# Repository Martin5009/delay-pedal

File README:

A 16-bit, FPGA-based digital delay pedal implementation.

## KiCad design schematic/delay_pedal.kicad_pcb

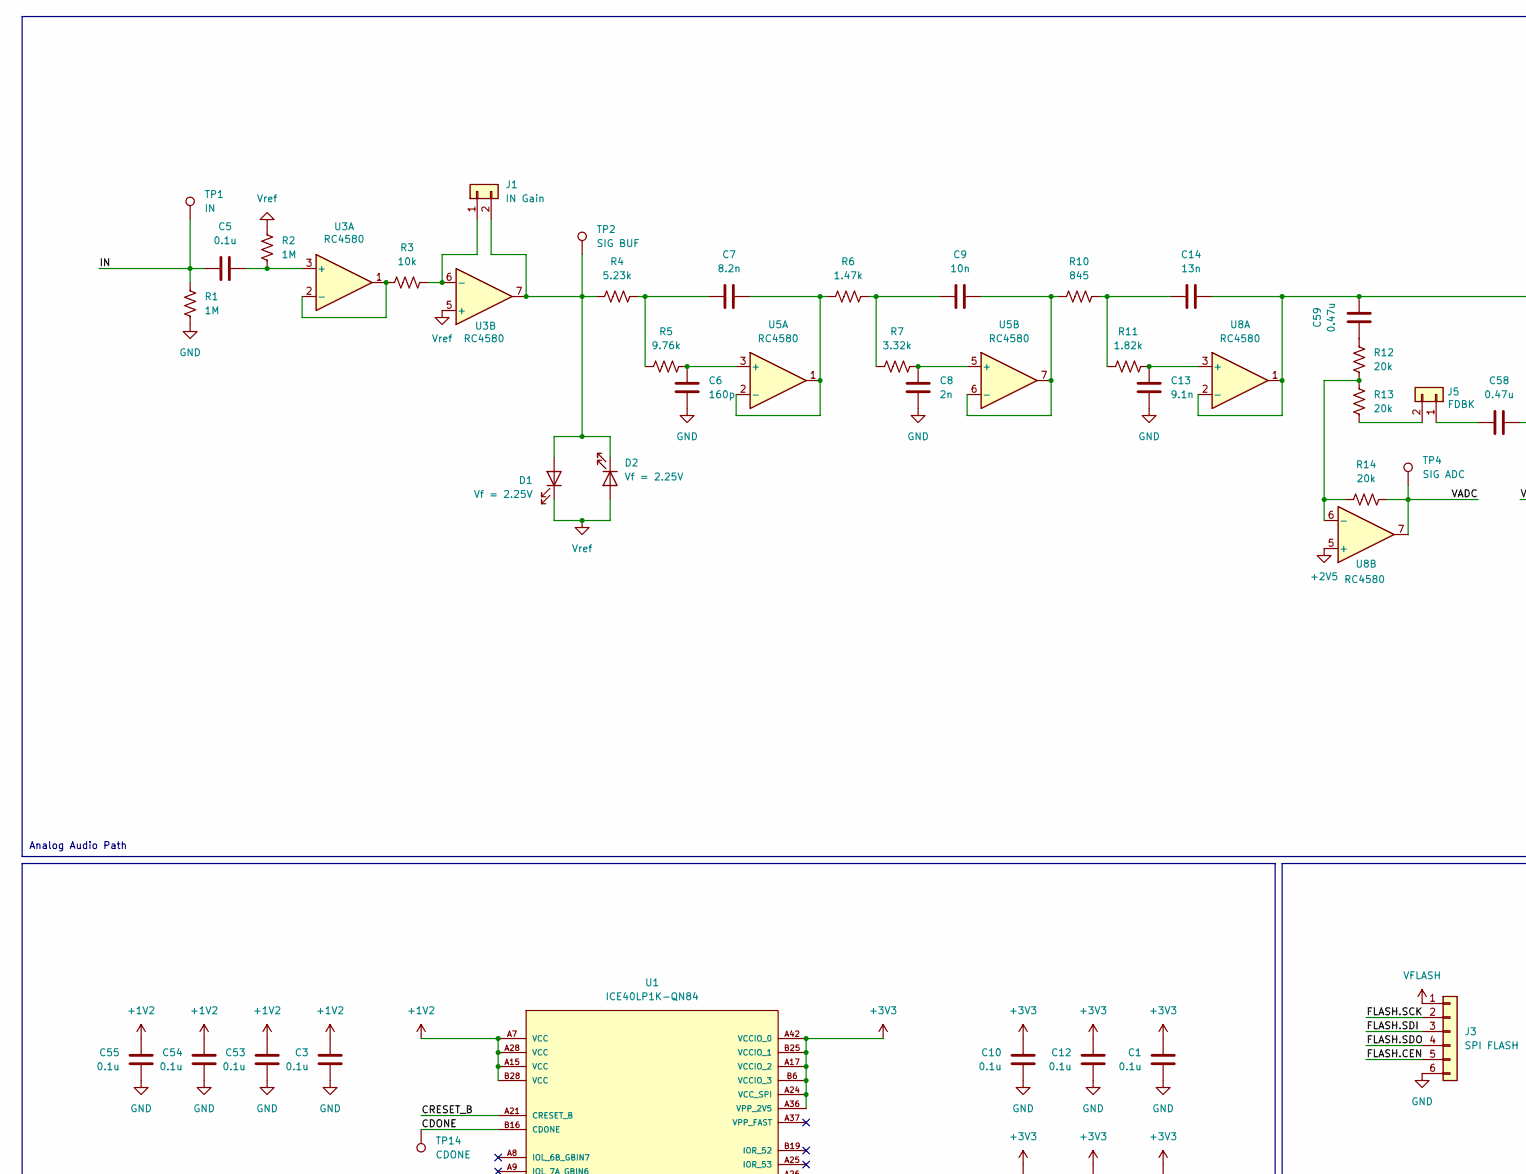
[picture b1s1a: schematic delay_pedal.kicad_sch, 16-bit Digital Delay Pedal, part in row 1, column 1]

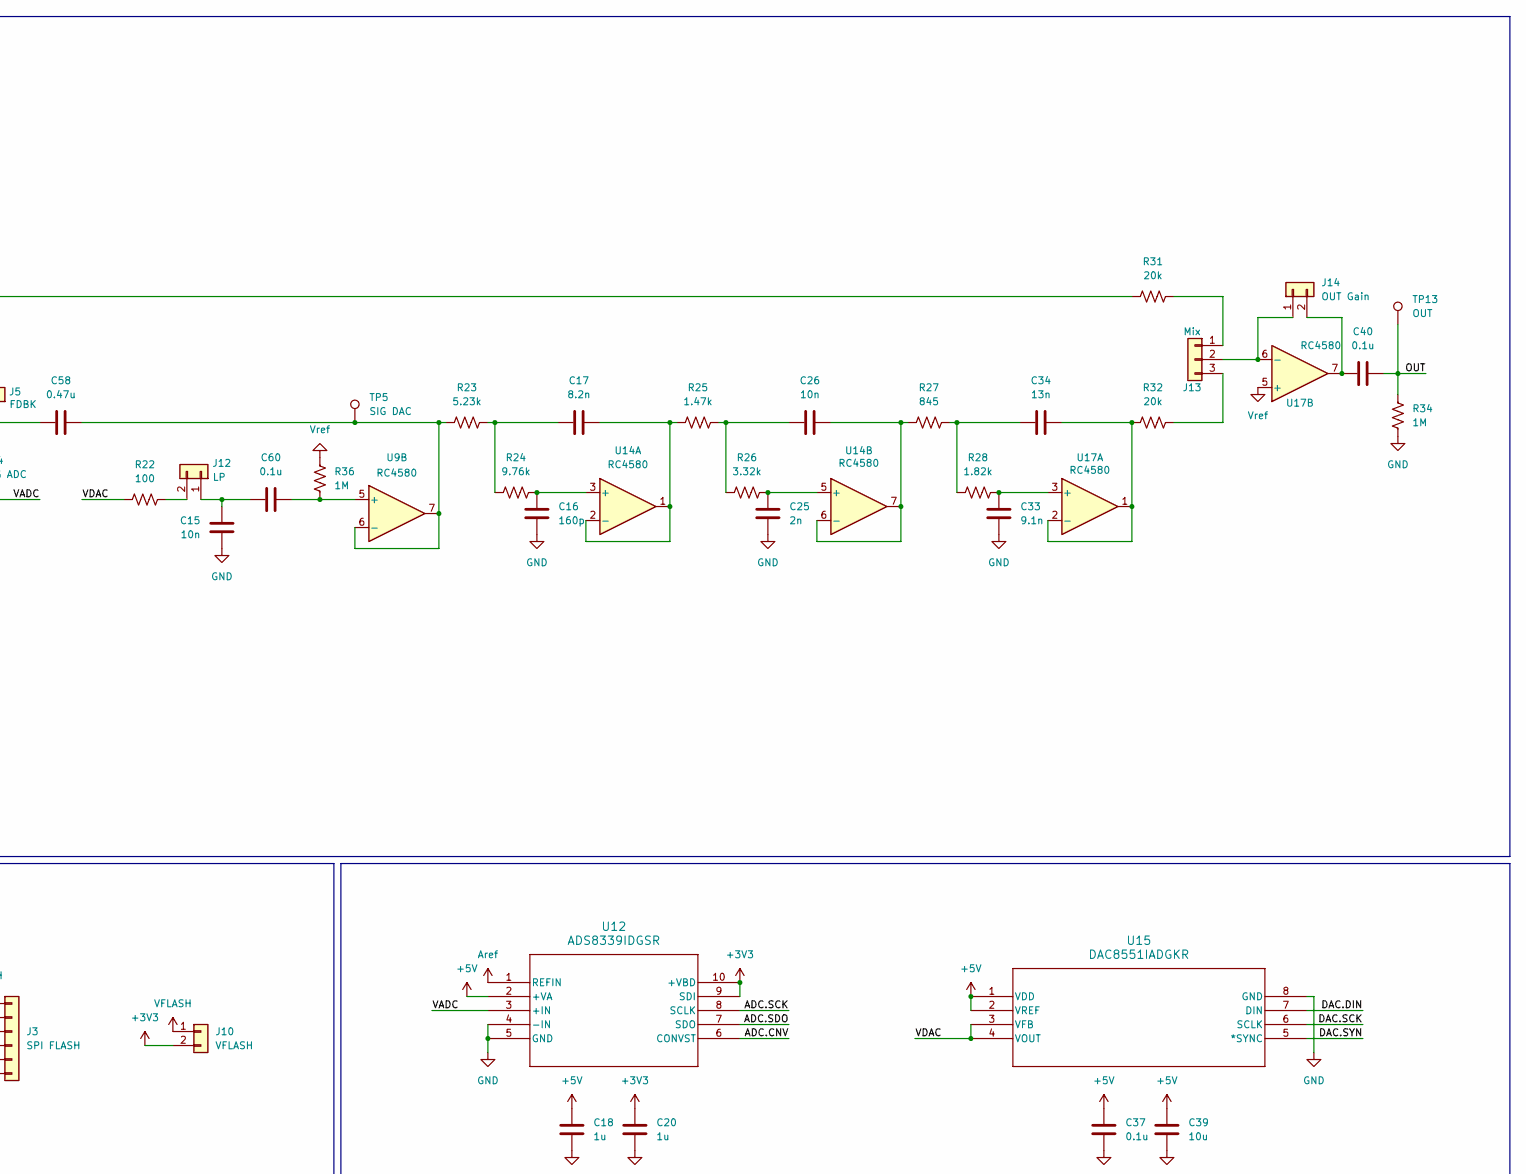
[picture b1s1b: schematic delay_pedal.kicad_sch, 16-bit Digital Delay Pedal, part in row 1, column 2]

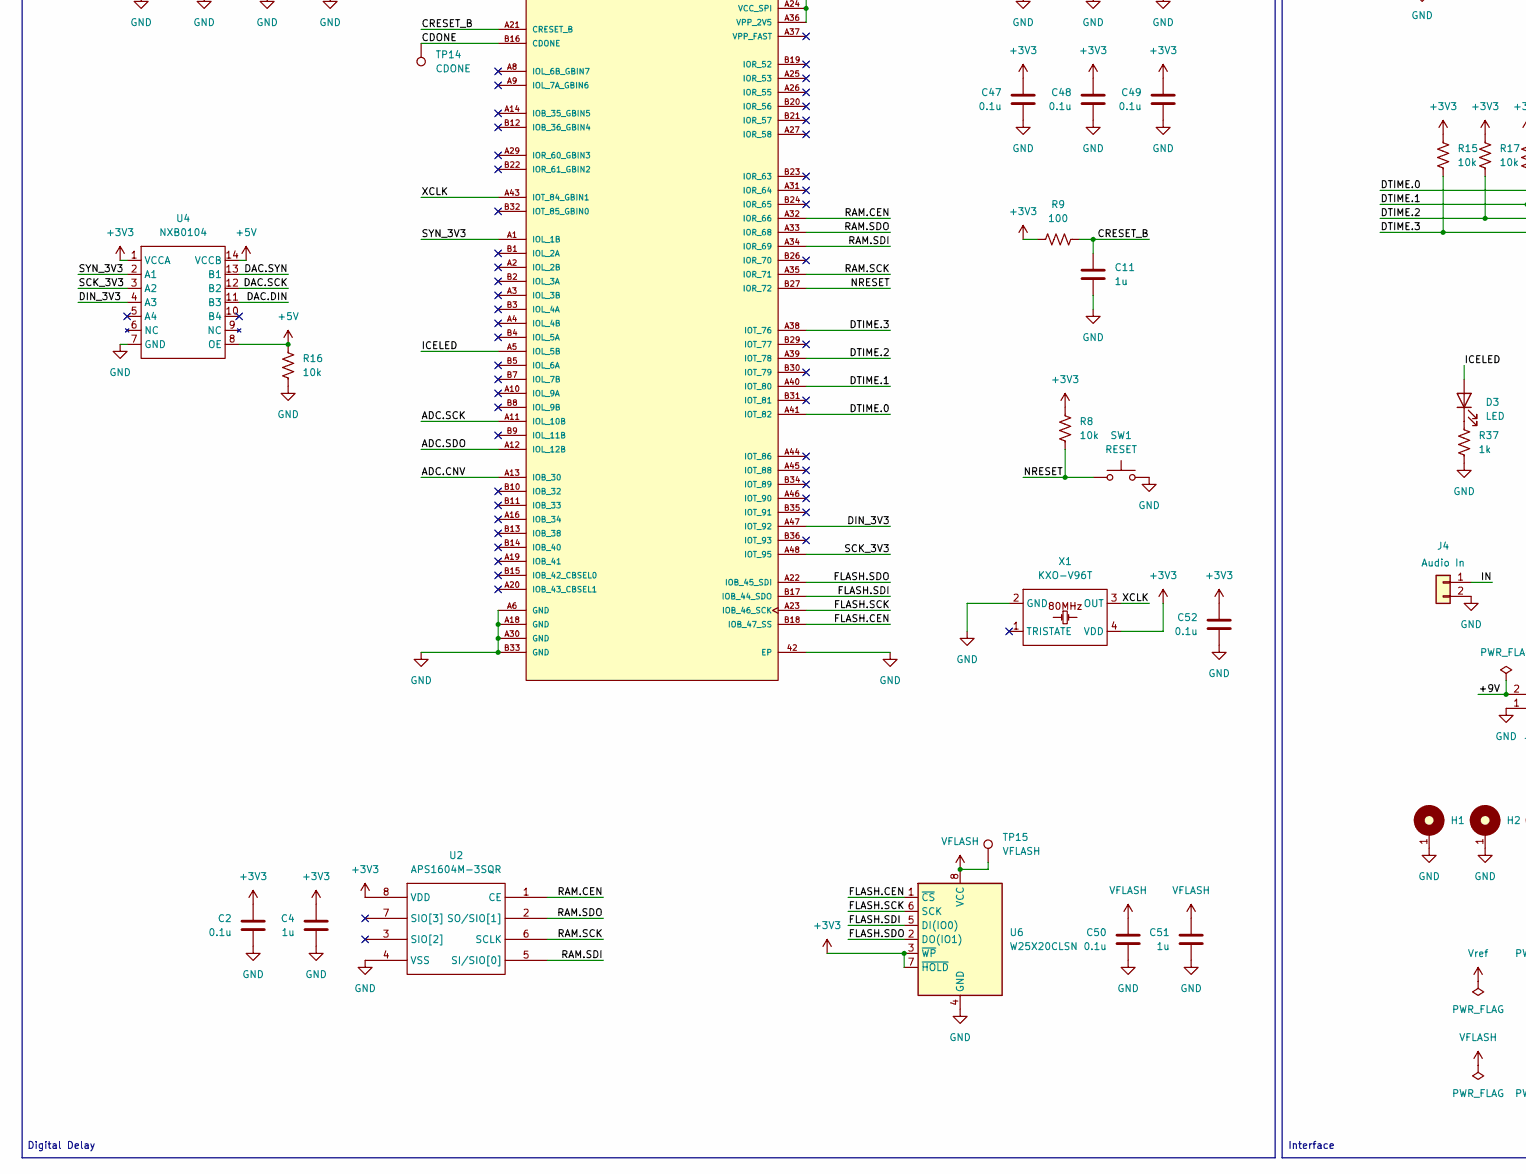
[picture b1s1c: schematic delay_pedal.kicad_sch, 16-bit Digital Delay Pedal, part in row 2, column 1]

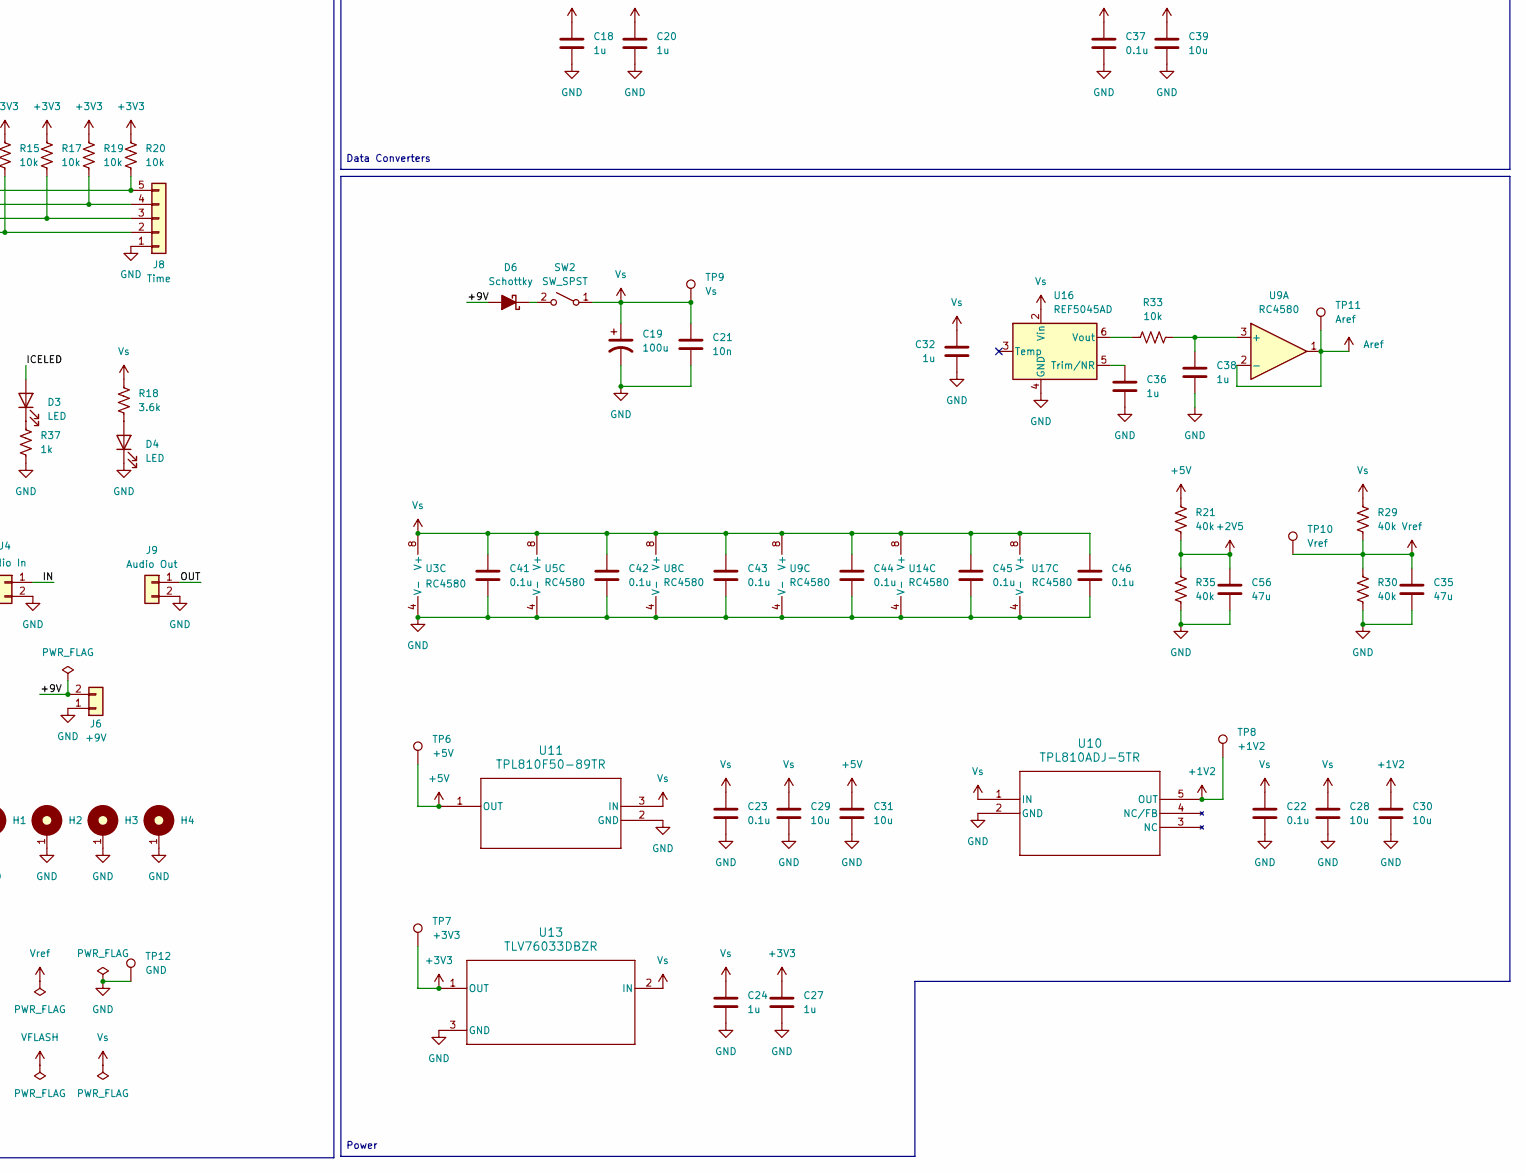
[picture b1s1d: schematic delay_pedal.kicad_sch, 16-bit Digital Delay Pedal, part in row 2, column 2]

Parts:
C1, C2, C3, C10, C12, C22, C23, C37, C41, C42, C43, C44, C45, C46, C47, C48, C49, C50, C52, C53, C54, C55: 0.1u; C_0603_1608Metric_Pad1.08x0.95mm_HandSolder
C4, C11, C18, C20, C24, C27, C32, C36, C38, C51: 1u; C_0603_1608Metric_Pad1.08x0.95mm_HandSolder
C5, C40, C60: 0.1u; C_1206_3216Metric_Pad1.33x1.80mm_HandSolder
C6, C16: 160p; C_0603_1608Metric_Pad1.08x0.95mm_HandSolder
C7, C17: 8.2n; C_0603_1608Metric_Pad1.08x0.95mm_HandSolder
C8, C25: 2n; C_0603_1608Metric_Pad1.08x0.95mm_HandSolder
C9, C15, C21, C26: 10n; C_0603_1608Metric_Pad1.08x0.95mm_HandSolder
C13, C33: 9.1n; C_0603_1608Metric_Pad1.08x0.95mm_HandSolder
C14, C34: 13n; C_0603_1608Metric_Pad1.08x0.95mm_HandSolder
C19: 100u; CP_Radial_D6.3mm_P2.50mm
C28, C29, C30, C31, C39: 10u; C_0603_1608Metric_Pad1.08x0.95mm_HandSolder
C35, C56: 47u; C_0603_1608Metric_Pad1.08x0.95mm_HandSolder
C58, C59: 0.47u; C_0603_1608Metric_Pad1.08x0.95mm_HandSolder
D1, D2: Vf = 2.25V; LED_0603_1608Metric_Pad1.05x0.95mm_HandSolder
D3, D4: LED; LED_0603_1608Metric_Pad1.05x0.95mm_HandSolder
D6: Schottky; D_SOD-323_HandSoldering
H1, H2, H3, H4: MountingHole_M3_3.2mm_Pad; MountingHole_3.2mm_Pad
J1: IN Gain; PinHeader_1x02_P2.54mm_Vertical
J3: SPI FLASH; PinHeader_1x06_P2.54mm_Vertical
J4: Audio In; PinHeader_1x02_P2.54mm_Vertical
J5: FDBK; PinHeader_1x02_P2.54mm_Vertical
J6: +9V; PinHeader_1x02_P2.54mm_Vertical
J8: Time; PinHeader_1x05_P2.54mm_Vertical
J9: Audio Out; PinHeader_1x02_P2.54mm_Vertical
J10: VFLASH; PinHeader_1x02_P2.54mm_Vertical
J12: LP; PinHeader_1x02_P2.54mm_Vertical
J13: Mix; PinHeader_1x03_P2.54mm_Vertical
J14: OUT Gain; PinHeader_1x02_P2.54mm_Vertical
R1, R2, R34, R36: 1M; R_0603_1608Metric_Pad0.98x0.95mm_HandSolder
R3, R8, R15, R16, R17, R19, R20, R33: 10k; R_0603_1608Metric_Pad0.98x0.95mm_HandSolder
R4, R23: 5.23k; R_0603_1608Metric_Pad0.98x0.95mm_HandSolder
R5, R24: 9.76k; R_0603_1608Metric_Pad0.98x0.95mm_HandSolder
R6, R25: 1.47k; R_0603_1608Metric_Pad0.98x0.95mm_HandSolder
R7, R26: 3.32k; R_0603_1608Metric_Pad0.98x0.95mm_HandSolder
R9, R22: 100; R_0603_1608Metric_Pad0.98x0.95mm_HandSolder
R10, R27: 845; R_0603_1608Metric_Pad0.98x0.95mm_HandSolder
R11, R28: 1.82k; R_0603_1608Metric_Pad0.98x0.95mm_HandSolder
R12, R13, R14, R31, R32: 20k; R_0603_1608Metric_Pad0.98x0.95mm_HandSolder
R18: 3.6k; R_0603_1608Metric_Pad0.98x0.95mm_HandSolder
R21, R29, R30, R35: 40k; R_0603_1608Metric_Pad0.98x0.95mm_HandSolder
R37: 1k; R_0603_1608Metric_Pad0.98x0.95mm_HandSolder
SW1: RESET; SW_PUSH_1P1T_6x3.5mm_H4.3_APEM_MJTP1243
SW2: SW_SPST; PinHeader_1x02_P2.54mm_Vertical
TP1: IN; TestPoint_THTPad_D1.0mm_Drill0.5mm
TP2: SIG BUF; TestPoint_THTPad_D1.0mm_Drill0.5mm
TP4: SIG ADC; TestPoint_THTPad_D1.0mm_Drill0.5mm
TP5: SIG DAC; TestPoint_THTPad_D1.0mm_Drill0.5mm
TP6: +5V; TestPoint_THTPad_D1.0mm_Drill0.5mm
TP7: +3V3; TestPoint_THTPad_D1.0mm_Drill0.5mm
TP8: +1V2; TestPoint_THTPad_D1.0mm_Drill0.5mm
TP9: Vs; TestPoint_THTPad_D1.0mm_Drill0.5mm
TP10: Vref; TestPoint_THTPad_D1.0mm_Drill0.5mm
TP11: Aref; TestPoint_THTPad_D1.0mm_Drill0.5mm
TP12: GND; TestPoint_THTPad_D1.0mm_Drill0.5mm
TP13: OUT; TestPoint_THTPad_D1.0mm_Drill0.5mm
TP14: CDONE; TestPoint_THTPad_D1.0mm_Drill0.5mm
TP15: VFLASH; TestPoint_THTPad_D1.0mm_Drill0.5mm
U1: ICE40LP1K-QN84; LATTICE_ICE40LP1K-QN84; PARTREV 3.4; DigiKey_Part_Number 220-1561-ND
U2: APS1604M-3SQR; SOP-8_3.9x4.9mm_P1.27mm
U3, U5, U8, U9, U14, U17: RC4580; SOIC-8_3.9x4.9mm_P1.27mm
U4: NXB0104; TSSOP-14_4.4x5mm_P0.65mm
U6: W25X20CLSN; SOIC-8_3.9x4.9mm_P1.27mm
U10: TPL810ADJ-5TR; SOT-23-5_HandSoldering
U11: TPL810F50-89TR; SOT-89-3_Handsoldering
U12: ADS8339IDGSR; VSSOP-10_3x3mm_P0.5mm
U13: TLV76033DBZR; SOT-89-3_Handsoldering
U15: DAC8551IADGKR; VSSOP-8_3x3mm_P0.65mm
U16: REF5045AD; SOIC-8_3.9x4.9mm_P1.27mm
X1: KXO-V96T; Oscillator_SMD_Abracon_ASE-4Pin_3.2x2.5mm

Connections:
+1V2: C3.1, C30.1, C53.1, C54.1, C55.1, TP8.1, U1.A7 (VCC), U1.A15 (VCC), U1.A28 (VCC), U1.B28 (VCC), U10.5 (OUT)
+2V5: C56.1, R21.2, R35.1, U8.5 (+)
+3V3: C1.1, C2.1, C4.1, C10.1, C12.1, C20.1, C27.1, C47.1, C48.1, C49.1, C52.1, J10.2, R8.1, R9.2, R15.1, R17.1, R19.1, R20.1, TP7.1, U1.A17 (VCCIO_2), U1.A24 (VCC_SPI), U1.A36 (VPP_2V5), U1.A42 (VCCIO_0), U1.B6 (VCCIO_3), U1.B25 (VCCIO_1), U2.8 (VDD), U4.1 (VCCA), U6.3 (~WP), U6.7 (~HOLD), U12.9 (SDI), U12.10 (+VBD), U13.1 (OUT), X1.4 (VDD)
+5V: C18.1, C31.1, C37.1, C39.1, R16.1, R21.1, TP6.1, U4.8 (OE), U4.14 (VCCB), U11.1 (OUT), U12.2 (+VA), U15.1 (VDD), U15.2 (VREF)
/+9V: D6.2 (A), J6.2
/ADC.CNV: U1.A13 (IOB_30), U12.6 (CONVST)
/ADC.SCK: U1.A11 (IOL_10B), U12.8 (SCLK)
/ADC.SDO: U1.A12 (IOL_12B), U12.7 (SDO)
/CDONE: TP14.1, U1.B16 (CDONE)
/CRESET_B: C11.1, R9.1, U1.A21 (CRESET_B)
/DAC.DIN: U4.11 (B3), U15.7 (DIN)
/DAC.SCK: U4.12 (B2), U15.6 (SCLK)
/DAC.SYN: U4.13 (B1), U15.5 (*SYNC)
/DIN_3V3: U1.A47 (IOT_92), U4.4 (A3)
/DTIME.0: J8.5, R20.2, U1.A41 (IOT_82)
/DTIME.1: J8.4, R19.2, U1.A40 (IOT_80)
/DTIME.2: J8.3, R17.2, U1.A39 (IOT_78)
/DTIME.3: J8.2, R15.2, U1.A38 (IOT_76)
/FLASH.CEN: J3.5, U1.B18 (IOB_47_SS), U6.1 (~CS)
/FLASH.SCK: J3.2, U1.A23 (IOB_46_SCK), U6.6 (SCK)
/FLASH.SDI: J3.3, U1.B17 (IOB_44_SDO), U6.5 (DI(IO0))
/FLASH.SDO: J3.4, U1.A22 (IOB_45_SDI), U6.2 (DO(IO1))
/ICELED: D3.2 (A), U1.A5 (IOL_5B)
/IN: C5.1, J4.1, R1.1, TP1.1
/NRESET: R8.2, SW1.1, U1.B27 (IOR_72)
/OUT: C40.2, J9.1, R34.1, TP13.1
/RAM.CEN: U1.A32 (IOR_66), U2.1 (CE)
/RAM.SCK: U1.A35 (IOR_71), U2.6 (SCLK)
/RAM.SDI: U1.A34 (IOR_69), U2.5 (SI/SIO[0])
/RAM.SDO: U1.A33 (IOR_68), U2.2 (SO/SIO[1])
/SCK_3V3: U1.A48 (IOT_95), U4.3 (A2)
/SYN_3V3: U1.A1 (IOL_1B), U4.2 (A1)
/VADC: R14.1, TP4.1, U8.7, U12.3 (+IN)
/VDAC: R22.2, U15.3 (VFB), U15.4 (VOUT)
/XCLK: U1.A43 (IOT_84_GBIN1), X1.3 (OUT)
Aref: TP11.1, U9.1, U9.2 (-), U12.1 (REFIN)
GND: C1.2, C2.2, C3.2, C4.2, C6.2, C8.2, C10.2, C11.2, C12.2, C13.2, C15.2, C16.2, C18.2, C19.2, C20.2, C21.2, C22.2, C23.2, C24.2, C25.2, C27.2, C28.2, C29.2, C30.2, C31.2, C32.2, C33.2, C35.2, C36.2, C37.2, C38.2, C39.2, C41.2, C42.2, C43.2, C44.2, C45.2, C46.2, C47.2, C48.2, C49.2, C50.2, C51.2, C52.2, C53.2, C54.2, C55.2, C56.2, D4.1 (K), H1.1, H2.1, H3.1, H4.1, J3.6, J4.2, J6.1, J8.1, J9.2, R1.2, R16.2, R30.2, R34.2, R35.2, R37.2, SW1.2, TP12.1, U1.42 (EP), U1.A6 (GND), U1.A18 (GND), U1.A30 (GND), U1.B33 (GND), U2.4 (VSS), U3.4 (V-), U4.7 (GND), U5.4 (V-), U6.4 (GND), U8.4 (V-), U9.4 (V-), U10.2 (GND), U11.2 (GND), U12.4 (-IN), U12.5 (GND), U13.3 (GND), U14.4 (V-), U15.8 (GND), U16.4 (GND), U17.4 (V-), X1.2 (GND)
unnamed: C7.1, R4.1, R5.2
unnamed: C9.1, R6.1, R7.2
unnamed: C14.1, R10.1, R11.2
unnamed: C17.1, R23.1, R24.2
unnamed: C26.1, R25.1, R26.2
unnamed: C34.1, R27.1, R28.2
unnamed: C59.1, R12.1
unnamed: D1.2 (A), D2.1 (K), J1.2, R4.2, TP2.1, U3.7
unnamed: D3.1 (K), R37.1
unnamed: D4.2 (A), R18.2
unnamed: D6.1 (K), SW2.2 (B)
unnamed: J1.1, R3.1, U3.6 (-)
unnamed: C58.1, J5.1
unnamed: J5.2, R13.2
unnamed: C15.1, C60.1, J12.1
unnamed: J12.2, R22.1
unnamed: J13.1, R31.1
unnamed: J13.2, J14.1, U17.6 (-)
unnamed: J13.3, R32.1
unnamed: C40.1, J14.2, U17.7
unnamed: C5.2, R2.2, U3.3 (+)
unnamed: R3.2, U3.1, U3.2 (-)
unnamed: C6.1, R5.1, U5.3 (+)
unnamed: C7.2, R6.2, U5.1, U5.2 (-)
unnamed: C8.1, R7.1, U5.5 (+)
unnamed: C9.2, R10.2, U5.6 (-), U5.7
unnamed: C13.1, R11.1, U8.3 (+)
unnamed: C14.2, C59.2, R31.2, U8.1, U8.2 (-)
unnamed: R12.2, R13.1, R14.2, U8.6 (-)
unnamed: C38.1, R33.1, U9.3 (+)
unnamed: C60.2, R36.2, U9.5 (+)
unnamed: C58.2, R23.2, TP5.1, U9.6 (-), U9.7
unnamed: C16.1, R24.1, U14.3 (+)
unnamed: C17.2, R25.2, U14.1, U14.2 (-)
unnamed: C25.1, R26.1, U14.5 (+)
unnamed: C26.2, R27.2, U14.6 (-), U14.7
unnamed: C36.1, U16.5 (Trim/NR)
unnamed: R33.2, U16.6 (Vout)
unnamed: C33.1, R28.1, U17.3 (+)
unnamed: C34.2, R32.2, U17.1, U17.2 (-)
VFLASH: C50.1, C51.1, J3.1, J10.1, TP15.1, U6.8 (VCC)
Vref: C35.1, D1.1 (K), D2.2 (A), R2.1, R29.2, R30.1, R36.1, TP10.1, U3.5 (+), U17.5 (+)
Vs: C19.1, C21.1, C22.1, C23.1, C24.1, C28.1, C29.1, C32.1, C41.1, C42.1, C43.1, C44.1, C45.1, C46.1, R18.1, R29.1, SW2.1 (A), TP9.1, U3.8 (V+), U5.8 (V+), U8.8 (V+), U9.8 (V+), U10.1 (IN), U11.3 (IN), U13.2 (IN), U14.8 (V+), U16.2 (Vin), U17.8 (V+)

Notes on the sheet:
Data Converters
Power
Analog Audio Path
Digital Delay
Interface

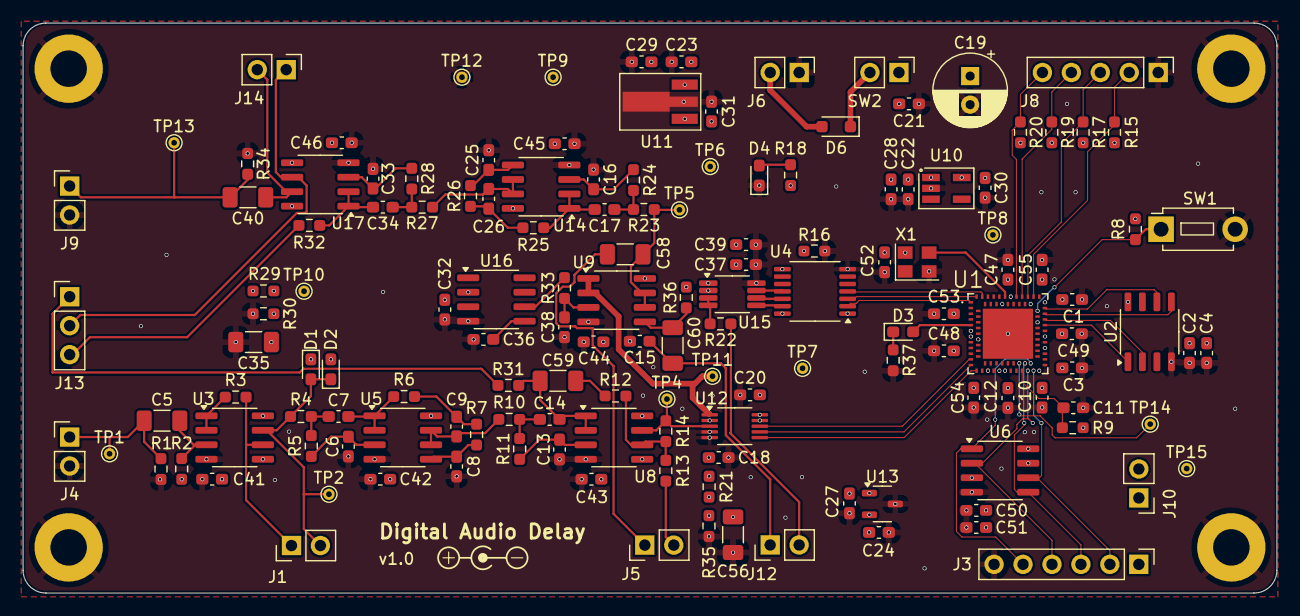
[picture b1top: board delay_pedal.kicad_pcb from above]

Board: 4 copper layers, 110.0 x 50.0 mm, 149 parts (0 on the bottom side), 80 nets.

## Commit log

2025-01-09 Added README
2025-01-10 Generated gtkwave files for delay_core_tb
2025-01-10 Added .gitignore file
2025-01-10 Moved .gitignore to root
2025-01-10 Populated README
2025-01-10 spi_controller now supports variable sck rate
2025-01-10 Reduced cycle time from 7us to 5us, raising effective sampling frequency to ~200kHz
2025-01-10 Added .DS_Store file to .gitignore
2025-01-10 delay_core no longer requires external clock pulse to start conversion
2025-01-16 Created fast_spi_controller, a module that supports SPI transactions at the system clock rate
2025-01-16 Delay time controllable with time[3:0]
2025-01-16 Added input buffer for time[3:0], now called dtime[3:0].
2025-01-17 Fixed fast_spi_controller
2025-01-17 Updated .gitignore to include .pcf and .sdc files
2025-01-17 Added constraint files for bitmap creation
2025-01-17 Added circuit schematic folder
2025-01-17 Updated pin assignments
2025-01-22 Fixed source of synthesis errors
2025-01-23 Added KiCAD files
2025-01-23 Updated schematic PDF
2025-01-23 Added missing capacitors to analog signal chain
2025-01-23 End of day
2025-01-23 Updated Schottky diode footprint
2025-01-24 Generated fabrication files
2025-01-24 Fixed footprint assignments
2025-01-24 Generated new gerbers
2025-01-25 Moved power supply LED close to power supply input
2025-01-30 Added silkscreen art
2025-01-31 Generated new fabrication files
2025-01-31 Updated .gitignore
